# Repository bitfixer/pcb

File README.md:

# pcb
A collection of open-source pcbs.

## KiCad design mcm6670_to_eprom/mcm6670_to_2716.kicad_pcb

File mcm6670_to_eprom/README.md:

An adapter to use an EPROM/EEPROM in place of an MCM6670 character generator, used in the TRS-80 Model 1.

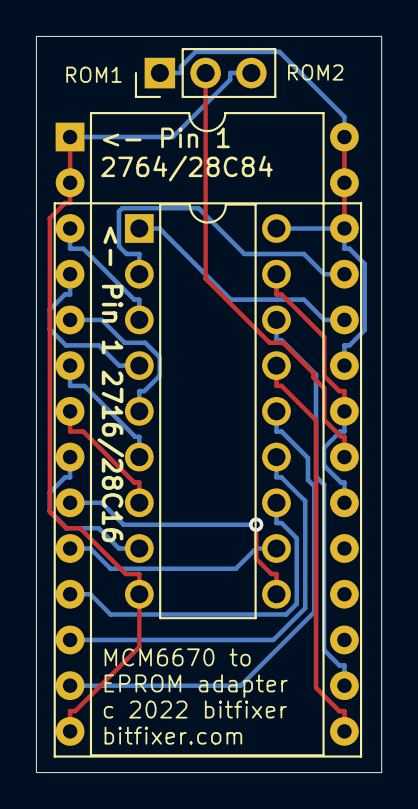
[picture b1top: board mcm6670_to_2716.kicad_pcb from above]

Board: 2 copper layers, 19.2 x 40.9 mm, 3 parts (0 on the bottom side), 19 nets.

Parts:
J1: MCM6670; DIP-18_W7.62mm
J2: Conn_02x14_Counter_Clockwise; DIP-28_W15.24mm
J3: Conn_01x03_Male; PinHeader_1x03_P2.54mm_Vertical

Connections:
+5V: J1.18, J2.23, J2.26, J2.27, J2.28, J3.1
A0: J1.7, J2.7
A1: J1.6, J2.6
A2: J1.5, J2.5
A3: J1.4, J2.4
A4: J1.3, J2.3
A5: J1.2, J2.25
A6: J1.1, J2.24
ASEL: J2.21, J3.2
CSBAR: J1.17, J2.20, J2.22
D0: J1.12, J2.11
D1: J1.13, J2.12
D2: J1.14, J2.13
D3: J1.15, J2.15
D4: J1.16, J2.16
GND: J1.9, J2.1, J2.2, J2.14, J3.3
RS1: J1.11, J2.10
RS2: J1.10, J2.9
RS3: J1.8, J2.8

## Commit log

2022-10-04 added pcb for mcm6670 to 2716 adapter
